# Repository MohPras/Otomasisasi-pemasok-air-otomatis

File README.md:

# Otomasisasi-pemasok-air-otomatis

Alat ini adalah alat yang digunakan untuk melakukan otomasisasi pemasok air secara otomatis. Cara kerja pertama saat kran air terbuka maka air akan masuk melewati pralon dan akan mengenai valve lalu otomatis valve akan terbuka selanjutnya valve akan mengirimkan sinyal ke flow sensor sehingga flo sensor akan aktif juga, Air pun akan masuk melewatinya. Kelebhian alat ini adalah kita dapat mengatur berapa liter air yang akan kita mau misal hanya 3 liter saja maka pada flow sensor kita atur agar dia melakukann perhitungan sampai 3 liter saja dan setelah itu flow sensor akan mengirimkan sinyal ke relay agar relay mentriger valve supaya tertutup. Outputnya hanya 3 liter saja air yang masuk.

Alat dan bahan yang di butuhkan:
- Flow sensor sebagai penghitung debit air
- Relay sebagai saklar otomatis
- Valve sebagai kran otomatis
- LCD sebagai dispay berapa liter air yang masuk

Design PCB

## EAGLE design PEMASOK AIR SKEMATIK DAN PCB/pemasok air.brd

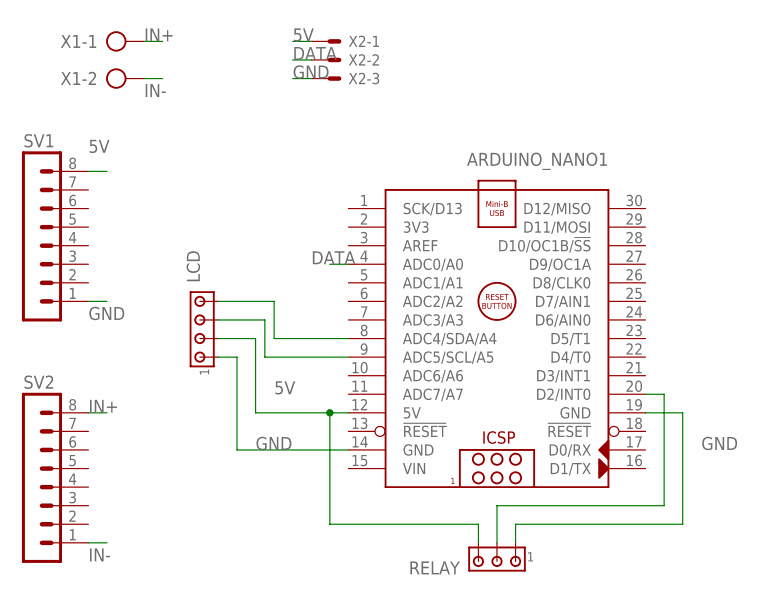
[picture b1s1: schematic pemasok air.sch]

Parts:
ARDUINO_NANO1: ARDUINO_NANO
LCD: MTA04-100; 10X04MTA
RELAY: MTA03-100; 10X03MTA
SV1, SV2: MA08-1
X1: AK500/2-H
X2: KK-156-3

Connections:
5V: ARDUINO_NANO1.12 (5V), LCD.2, RELAY.3, SV1.8, X2.1
DATA: ARDUINO_NANO1.4 (ADC0/A0), X2.2
GND: ARDUINO_NANO1.14 (GND), ARDUINO_NANO1.19 (GND), LCD.1, RELAY.1, SV1.1, X2.3
IN+: SV2.8, X1.1
IN-: SV2.1, X1.2
unnamed: ARDUINO_NANO1.8 (ADC4/SDA/A4), LCD.4
unnamed: ARDUINO_NANO1.9 (ADC5/SCL/A5), LCD.3
unnamed: ARDUINO_NANO1.20 (D2/INT0), RELAY.2
VIN: ARDUINO_NANO1.15 (VIN)

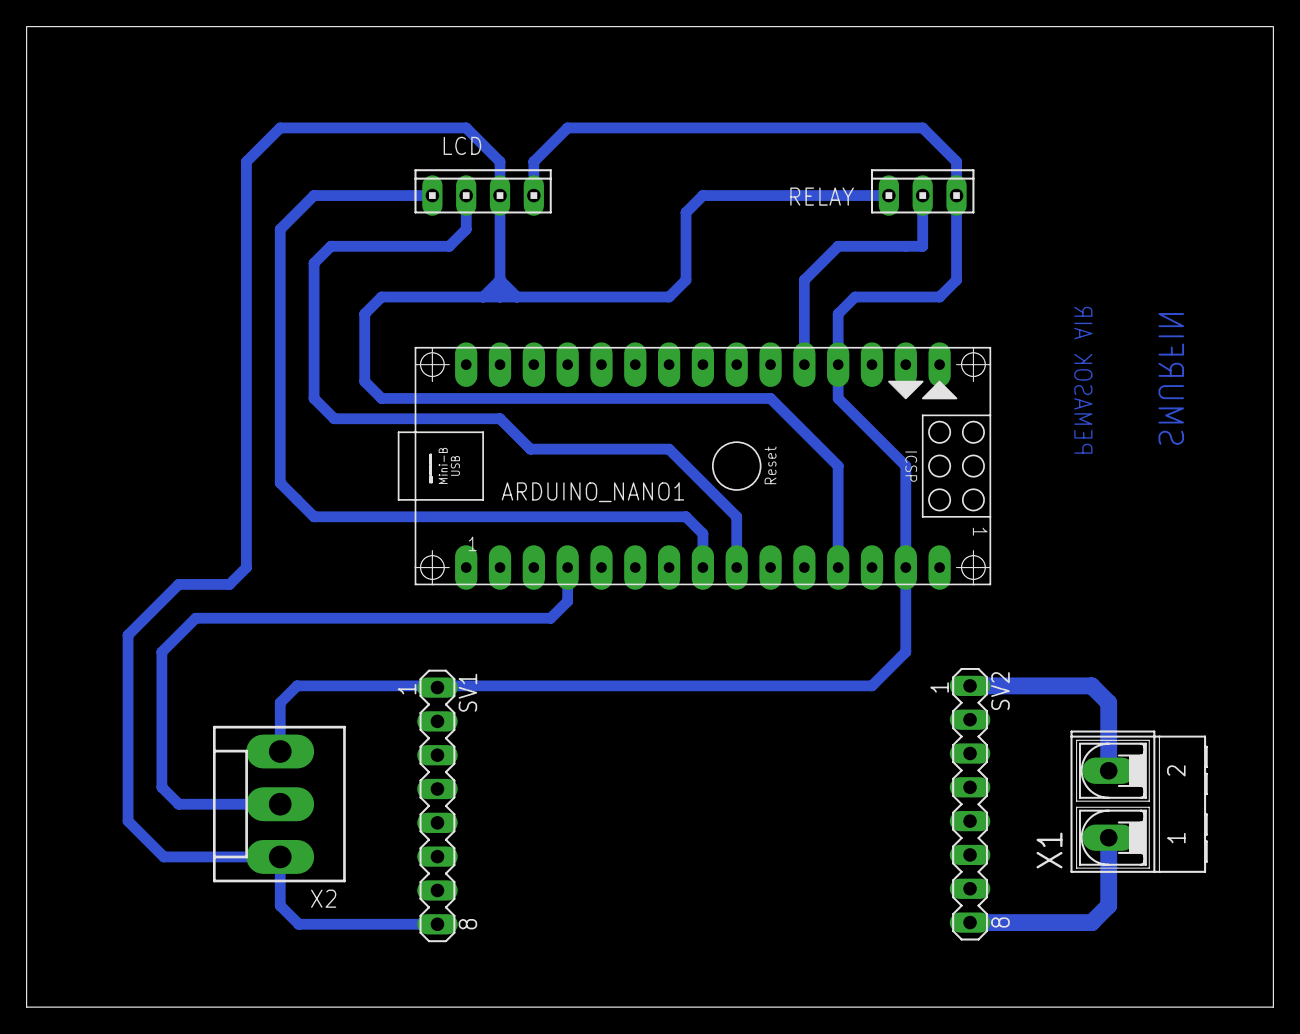
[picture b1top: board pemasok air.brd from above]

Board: 2 copper layers, 93.7 x 73.7 mm, 7 parts (0 on the bottom side), 8 nets.
